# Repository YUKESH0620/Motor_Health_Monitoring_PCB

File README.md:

# Motor Health Monitoring System using 8051

**Embedded Hardware–Firmware Co-Design Project**

---

## Project Overview

The **Motor Health Monitoring System** is an embedded systems project designed to monitor the operational health of an electric motor and protect it from unsafe conditions.

The project integrates:

* A structured hardware design
* Bare-metal embedded control logic
* Simulation-based validation
* Professional documentation practices

The focus is on **learning, reliability, and design clarity**, following workflows commonly used in industry and academia.

---

## System Purpose

* Monitor key motor parameters
* Detect abnormal operating conditions
* Automatically disable the motor under fault
* Provide clear visual and UART-based feedback
* Enable validation without physical hardware

---

## System Operation Flow

* System initialization

* Peripheral setup

* Sensor sampling

* Data filtering

* Threshold comparison

* Fault decision

* Motor control update

* Display & UART update

* Continuous monitoring loop

## Block Diagram

```
Power Input
    │
    V
Voltage Regulation
    │
    V
Microcontroller (8051)
 |--> Sensor Interface
 |   |--> Current
 |   |--> Temperature
 |   |--> Vibration
 |   |--> IR Sensor
 |
 |--> Motor Driver (PWM Control)
 |--> Display (OLED)
 |--> Keypad Interface
 |--> UART Debug Interface
```

---

## System Summary

| Aspect         | Description                         |
| -------------- | ----------------------------------- |
| Controller     | AT89C51 (8051 architecture)         |
| Control Method | Bare-metal                          |
| Sensors        | Current, Temperature, Vibration, IR |
| Motor Control  | PWM-based with fault shutdown       |
| Display        | OLED (I²C)                          |
| User Input     | 4×4 Keypad                          |
| Communication  | UART                                |
| Validation     | Proteus Simulation                  |
| PCB Status     | Not fabricated                      |

---

## Design Artifacts

The repository contains:

* Complete hardware schematics

* PCB layout and 3D models (design stage)

* Proteus simulation files

* Modular firmware source code

* Structured documentation

---

# Schematic Diagram

# PCB Layout

# 3D PCB View

---

## Electrical Specifications

| Parameter                  | Value                         |
|----------------------------|-------------------------------|
| Supply Voltage             | 5 V DC                        |
| MCU Logic Level            | 5 V                           |
| Over-Current Threshold     | 15 A                          |
| Over-Temperature Threshold | 70 °C                         |
| Communication Baud Rate    | Configurable (UART)           |
| Fault Response Time        | Deterministic (loop-based)    |

---

# Simulation_v1

The system was simulated using **Proteus 8.1 Professional software** to validate firmware behavior and system-level logic prior to hardware availability.
The AT89C51 microcontroller, UART interface, motor control logic, fault indicators, and peripheral connections were instantiated according to the schematic.

## Proteus Schematic

Sensor inputs were emulated using adjustable sources to exercise overcurrent and overtemperature fault paths. UART output was used to confirm firmware execution flow and system state transitions. Motor operation was verified logically through enable signals and status indicators rather than physical motor dynamics.

Due to simulator limitations with mixed-signal SPI peripherals on the 8051 core, ADC behavior was validated at firmware logic level. Electrical accuracy of sensor interfaces is planned for validation on physical hardware.

---

## Validation Strategy

* Firmware behavior validated using Proteus simulation at system and logic level

* UART used as the primary observation and debug interface to confirm system states

* Motor control and global shutdown behavior verified through control signals and status indicators

* Fault detection, latching, and recovery logic validated against defined thresholds

* Sensor behavior emulated to exercise fault paths; ADC interface validated at firmware logic level

* Simulation limitations identified and documented; full electrical validation planned on physical hardware

* No dependency on physical PCB availability for firmware and system-level validation

---

## Repository Organization

* **Hardware**
  Contains schematic, PCB, simulation files, and hardware documentation

* **Firmware**
  Contains source code, configuration files, and firmware documentation

Each section includes its own detailed README.

---

## Current Project Status

*  Requirements defined
*  Hardware designed
*  Simulation validated
*  Firmware structured and built
*  PCB fabrication pending

---

## Future Enhancements

* Physical PCB manufacturing
* Bench testing with real motors
* Data logging and diagnostics
* IoT expansion via external gateway
* Advanced fault analytics

---

## Author

**YUKESH**
B.E. Electrical and Electronics Engineering

---

## License

This project is intended for **educational and non-commercial use**.
All materials are shared to support learning, experimentation, and academic review.

---

## Closing Note

This project demonstrates a **complete embedded system lifecycle** - from concept and schematic design to firmware integration and simulation-based validation - following practices aligned with real-world engineering workflows.

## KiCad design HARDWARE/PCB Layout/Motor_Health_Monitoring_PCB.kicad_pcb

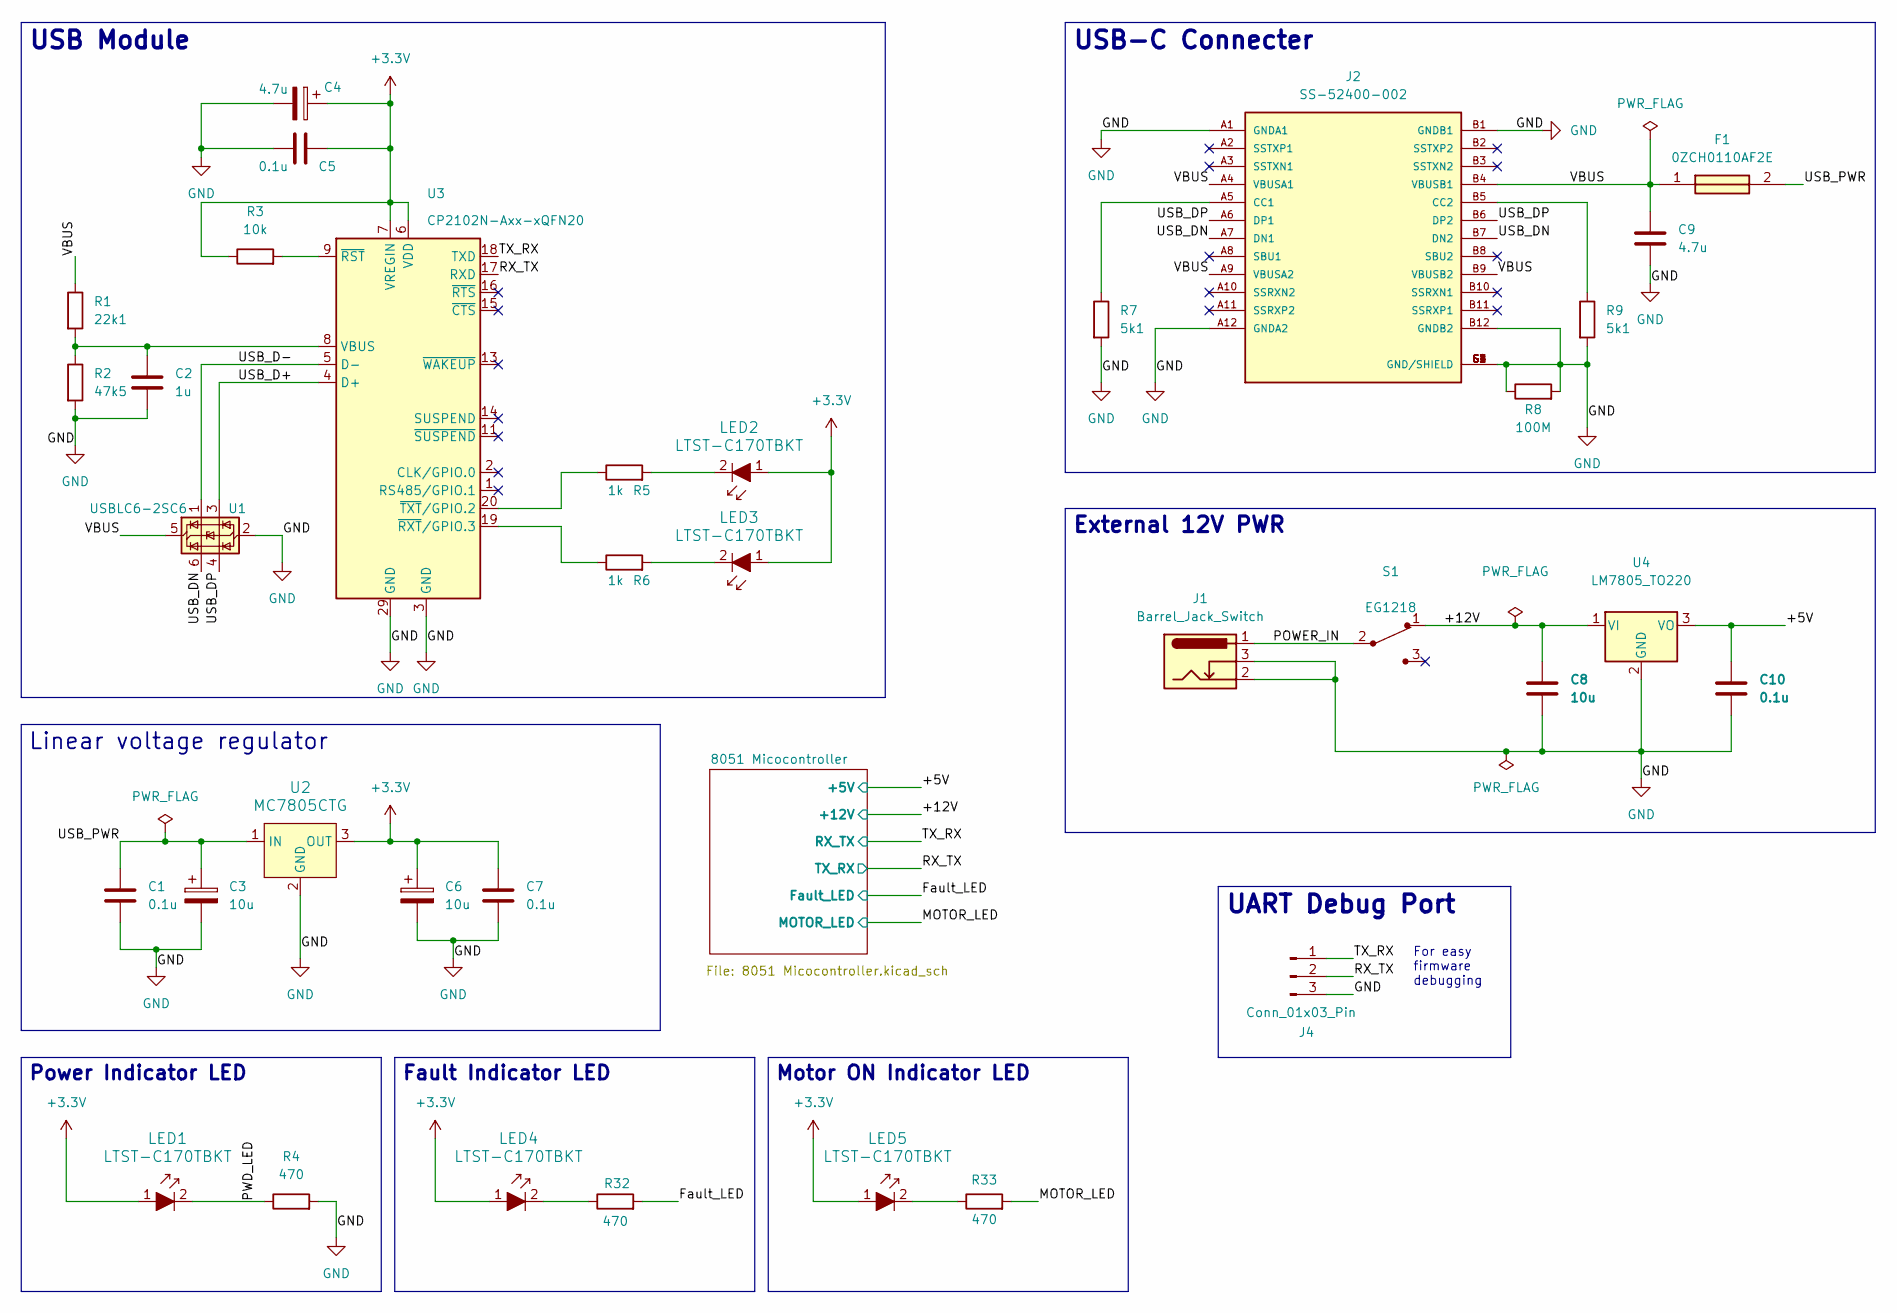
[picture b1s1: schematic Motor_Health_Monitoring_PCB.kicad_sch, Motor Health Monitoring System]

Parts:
C1, C5, C7: 0.1u; C_0805_2012Metric
C2: 1u; C_0805_2012Metric
C3, C6: 10u; T491A
C4: 4.7u; T491A
C8: 10u; C_Disc_D5.0mm_W2.5mm_P2.50mm
C9: 4.7u; C_0805_2012Metric
C10: 0.1u; C_Disc_D5.0mm_W2.5mm_P2.50mm
F1: 0ZCH0110AF2E; FUSC3226X100N; Manufacturer_Part_Number 0ZCH0110AF2E
J1: Barrel_Jack_Switch; BarrelJack_Horizontal
J2: SS-52400-002; BELFUSE_SS-52400-002; PARTREV A0
J4: Conn_01x03_Pin; PinHeader_1x03_P2.54mm_Vertical
LED1, LED2, LED3, LED4, LED5: LTST-C170TBKT; LED_0805_2012Metric_Pad1.15x1.40mm_HandSolder; MPN LTST-C170TBKT; Digi-Key_PN 160-1579-1-ND
R1: 22k1; R_0805_2012Metric
R2: 47k5; R_0805_2012Metric
R3: 10k; R_0805_2012Metric
R4, R32, R33: 470; R_0805_2012Metric
R5, R6: 1k; R_0805_2012Metric
R7, R9: 5k1; R_0805_2012Metric
R8: 100M; R_0805_2012Metric
S1: EG1218; Switch_Slide_11.6x4mm_EG1218; MPN EG1218; Digi-Key_PN EG1903-ND
U1: USBLC6-2SC6; SOT-23-6
U2: MC7805CTG; TO-220-3; MPN MC7805CTG; Digi-Key_PN MC7805CTGOS-ND
U3: CP2102N-Axx-xQFN20; QFN50P500X500X100-29N
U4: LM7805_TO220; TO-220-3_Vertical

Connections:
+3.3V: C4.1, C5.2, C6.1, C7.1, LED1.1, LED2.1, LED3.1, LED4.1, LED5.1, R3.1, U2.3 (OUT), U3.6 (VDD), U3.7 (VREGIN)
/+5V: C10.1, U4.3 (VO); also elsewhere on the board
/+12V: C8.1, S1.1, U4.1 (VI); also elsewhere on the board
/Fault_LED: R32.2; also elsewhere on the board
/MOTOR_LED: R33.2; also elsewhere on the board
/POWER_IN: J1.1, S1.2
/PWD_LED: LED1.2, R4.1
/RX_TX: J4.2, U3.17 (RXD); also elsewhere on the board
/TX_RX: J4.1, U3.18 (TXD); also elsewhere on the board
/USB_D+: U1.3 (I/O2), U3.4 (D+)
/USB_D-: U1.1 (I/O1), U3.5 (D-)
/USB_DN: J2.A7 (DN1), J2.B7 (DN2), U1.6 (I/O1)
/USB_DP: J2.A6 (DP1), J2.B6 (DP2), U1.4 (I/O2)
/USB_PWR: C1.1, C3.1, F1.2, U2.1 (IN)
/VBUS: C9.1, F1.1, J2.A4 (VBUSA1), J2.A9 (VBUSA2), J2.B4 (VBUSB1), J2.B9 (VBUSB2), R1.1, U1.5 (VBUS)
GND: C1.2, C2.2, C3.2, C4.2, C5.1, C6.2, C7.2, C8.2, C9.2, C10.2, J1.2, J1.3, J2.A1 (GNDA1), J2.A12 (GNDA2), J2.B1 (GNDB1), J2.B12 (GNDB2), J2.G1 (GND/SHIELD), J2.G2 (GND/SHIELD), J2.G3 (GND/SHIELD), J2.G4 (GND/SHIELD), J2.S1 (GND/SHIELD), J2.S2 (GND/SHIELD), J2.S3 (GND/SHIELD), J2.S4 (GND/SHIELD), J4.3, R2.2, R4.2, R7.2, R8.1, R8.2, R9.2, U1.2 (GND), U2.2 (GND), U3.3 (GND), U3.12 (GND), U3.21 (GND), U3.29 (GND), U4.2 (GND); also elsewhere on the board
unnamed: J2.A5 (CC1), R7.1
unnamed: J2.B5 (CC2), R9.1
unnamed: LED2.2, R5.2
unnamed: LED3.2, R6.2
unnamed: LED4.2, R32.1
unnamed: LED5.2, R33.1
unnamed: C2.1, R1.2, R2.1, U3.8 (VBUS)
unnamed: R3.2, U3.9 (~RST)
unnamed: R6.1, U3.19 (~RXT/GPIO.3)
unnamed: R5.1, U3.20 (~TXT/GPIO.2)

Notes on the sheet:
For easy firmware debugging
Power Indicator LED
Motor ON Indicator LED
Fault Indicator LED
USB Module
USB-C Connecter
External 12V PWR
UART Debug Port
Linear voltage regulator

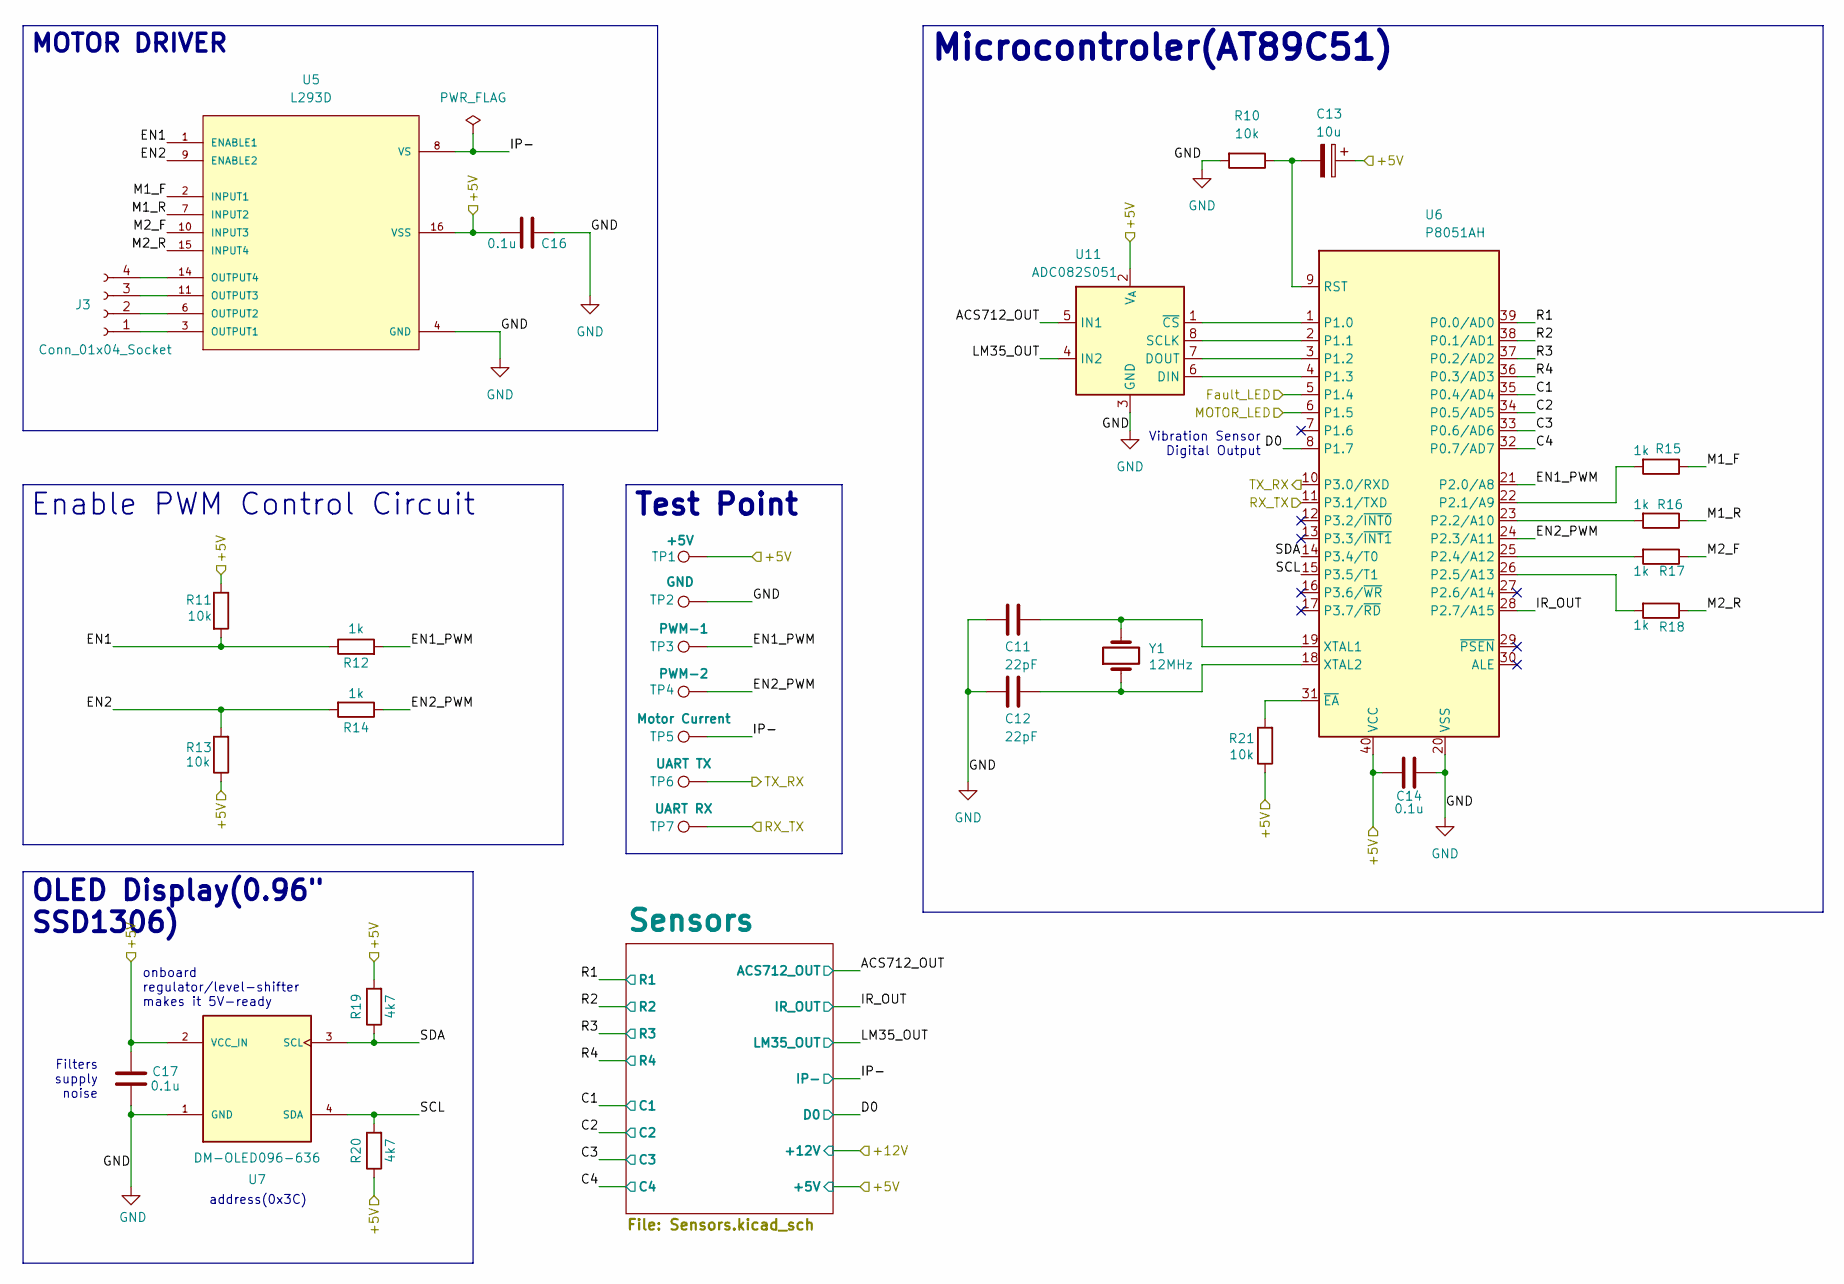
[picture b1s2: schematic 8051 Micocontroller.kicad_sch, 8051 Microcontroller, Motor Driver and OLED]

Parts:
C11, C12: 22pF; C_0805_2012Metric
C13: 10u; C_0805_2012Metric
C14, C16, C17: 0.1u; C_0805_2012Metric
J3: Conn_01x04_Socket; TerminalBlock_Phoenix_PT-1,5-4-5.0-H_1x04_P5.00mm_Horizontal
R10, R11, R13, R21: 10k; R_0805_2012Metric
R12, R14, R15, R16, R17, R18: 1k; R_0805_2012Metric
R19, R20: 4k7; R_0805_2012Metric
TP1: +5V; TestPoint_Pad_D2.0mm
TP2: GND; TestPoint_Pad_D2.0mm
TP3: PWM-1; TestPoint_Pad_D2.0mm
TP4: PWM-2; TestPoint_Pad_D2.0mm
TP5: Motor Current; TestPoint_Pad_D2.0mm
TP6: UART TX; TestPoint_Pad_D2.0mm
TP7: UART RX; TestPoint_Pad_D2.0mm
U5: L293D; DIP880W50P254L2000H510Q16
U6: P8051AH; DIP-40_W15.24mm
U7: DM-OLED096-636; MODULE_DM-OLED096-636; PARTREV 2018-09-10
U11: ADC082S051; VSSOP-8_3x3mm_P0.65mm
Y1: 12MHz; Crystal_SMD_5032-2Pin_5.0x3.2mm_HandSoldering

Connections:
/8051 Micocontroller/ACS712_OUT: U11.5 (IN1); also elsewhere on the board
/8051 Micocontroller/C1: U6.35 (P0.4/AD4); also elsewhere on the board
/8051 Micocontroller/C2: U6.34 (P0.5/AD5); also elsewhere on the board
/8051 Micocontroller/C3: U6.33 (P0.6/AD6); also elsewhere on the board
/8051 Micocontroller/C4: U6.32 (P0.7/AD7); also elsewhere on the board
/8051 Micocontroller/D0: U6.8 (P1.7); also elsewhere on the board
/8051 Micocontroller/EN1: R11.2, R12.1, U5.1 (ENABLE1)
/8051 Micocontroller/EN1_PWM: R12.2, TP3.1, U6.21 (P2.0/A8)
/8051 Micocontroller/EN2: R13.2, R14.2, U5.9 (ENABLE2)
/8051 Micocontroller/EN2_PWM: R14.1, TP4.1, U6.24 (P2.3/A11)
/8051 Micocontroller/IP-: TP5.1, U5.8 (VS); also elsewhere on the board
/8051 Micocontroller/IR_OUT: U6.28 (P2.7/A15); also elsewhere on the board
/8051 Micocontroller/LM35_OUT: U11.4 (IN2); also elsewhere on the board
/8051 Micocontroller/M1_F: R15.1, U5.2 (INPUT1)
/8051 Micocontroller/M1_R: R16.1, U5.7 (INPUT2)
/8051 Micocontroller/M2_F: R17.1, U5.10 (INPUT3)
/8051 Micocontroller/M2_R: R18.1, U5.15 (INPUT4)
/8051 Micocontroller/R1: U6.39 (P0.0/AD0); also elsewhere on the board
/8051 Micocontroller/R2: U6.38 (P0.1/AD1); also elsewhere on the board
/8051 Micocontroller/R3: U6.37 (P0.2/AD2); also elsewhere on the board
/8051 Micocontroller/R4: U6.36 (P0.3/AD3); also elsewhere on the board
/8051 Micocontroller/SCL: R20.2, U6.15 (P3.5/T1), U7.4 (SDA)
/8051 Micocontroller/SDA: R19.1, U6.14 (P3.4/T0), U7.3 (SCL)
/+5V: C13.1, C14.1, C16.1, C17.2, R11.1, R13.1, R19.2, R20.1, R21.1, TP1.1, U5.16 (VSS), U6.40 (VCC), U7.2 (VCC_IN), U11.2 (V_{A}); also elsewhere on the board
/Fault_LED: U6.5 (P1.4); also elsewhere on the board
/MOTOR_LED: U6.6 (P1.5); also elsewhere on the board
/RX_TX: TP6.1, U6.10 (P3.0/RXD); also elsewhere on the board
/TX_RX: TP7.1, U6.11 (P3.1/TXD); also elsewhere on the board
GND: C11.2, C12.2, C14.2, C16.2, C17.1, R10.2, TP2.1, U5.4 (GND), U5.5 (GND), U5.12 (GND), U5.13 (GND), U6.20 (VSS), U7.1 (GND), U11.3 (GND); also elsewhere on the board
unnamed: J3.1, U5.3 (OUTPUT1)
unnamed: J3.2, U5.6 (OUTPUT2)
unnamed: J3.3, U5.11 (OUTPUT3)
unnamed: J3.4, U5.14 (OUTPUT4)
unnamed: R15.2, U6.22 (P2.1/A9)
unnamed: R16.2, U6.23 (P2.2/A10)
unnamed: R17.2, U6.25 (P2.4/A12)
unnamed: R18.2, U6.26 (P2.5/A13)
unnamed: C13.2, R10.1, U6.9 (RST)
unnamed: C11.1, U6.19 (XTAL1), Y1.2
unnamed: C12.1, U6.18 (XTAL2), Y1.1
unnamed: R21.2, U6.31 (~EA)
unnamed: U6.4 (P1.3), U11.6 (DIN)
unnamed: U6.3 (P1.2), U11.7 (DOUT)
unnamed: U6.2 (P1.1), U11.8 (SCLK)
unnamed: U6.1 (P1.0), U11.1 (~CS)

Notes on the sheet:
onboard regulator/level-shifter makes it 5V-ready
address(0x3C)
Vibration Sensor Digital Output
Filters supply noise
Test Point
MOTOR DRIVER
Microcontroler(AT89C51)
Enable PWM Control Circuit
OLED Display(0.96" SSD1306)

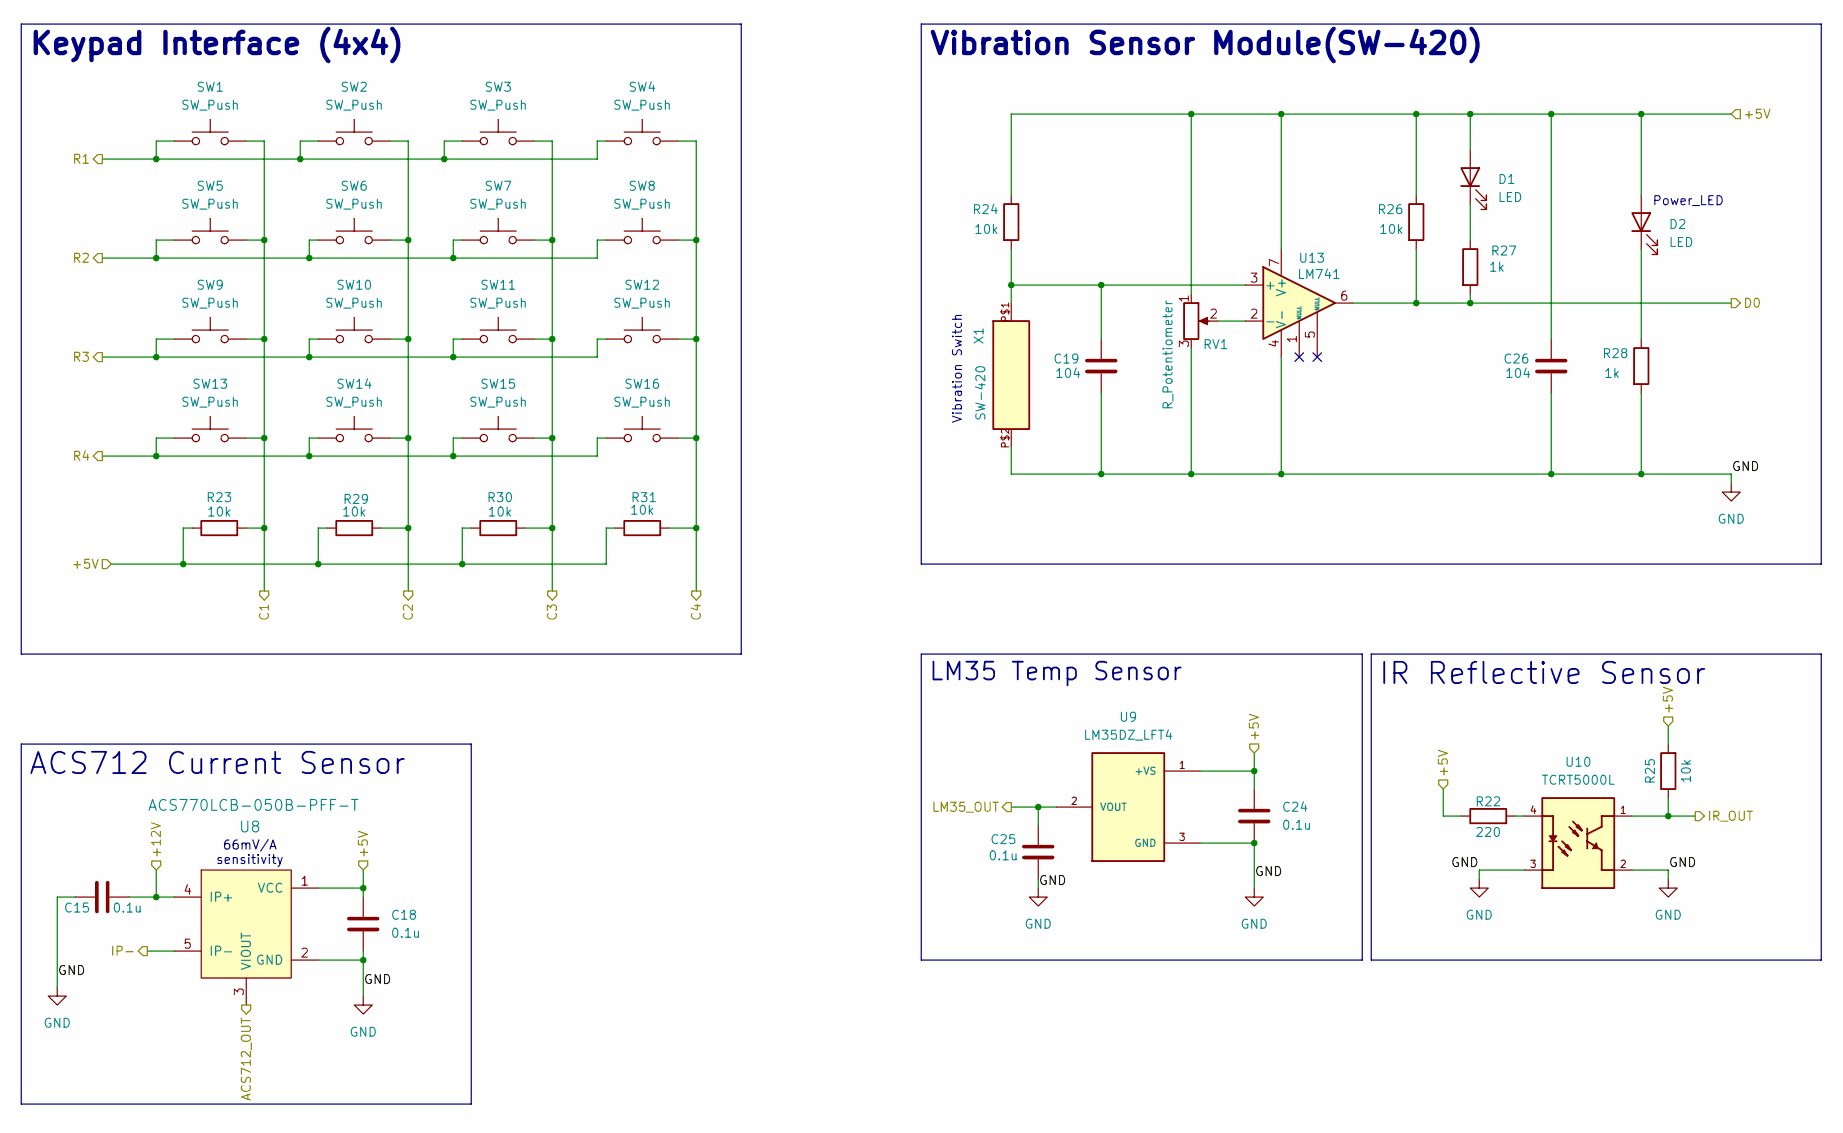
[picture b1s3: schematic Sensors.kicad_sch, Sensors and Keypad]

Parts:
C15, C18, C24, C25: 0.1u; C_0805_2012Metric
C19, C26: 104; C_0805_2012Metric
D1, D2: LED; LED_0805_2012Metric_Pad1.15x1.40mm_HandSolder
R22: 220; R_0805_2012Metric
R23, R24, R25, R26, R29, R30, R31: 10k; R_0805_2012Metric
R27, R28: 1k; R_0805_2012Metric
RV1: R_Potentiometer; Potentiometer_Bourns_3266Y_Vertical
SW1, SW2, SW3, SW4, SW5, SW6, SW7, SW8, SW9, SW10, SW11, SW12, SW13, SW14, SW15, SW16: SW_Push; SW_PUSH_1P1T_6x3.5mm_H5.0_APEM_MJTP1250
U8: ACS770LCB-050B-PFF-T; CB-5_Formed_Leads; MPN ACS770LCB-050B-PFF-T; Digi-Key_PN 620-1541-5-ND
U9: LM35DZ_LFT4; IC_LM35DZ_LFT4; PARTREV H
U10: TCRT5000L; XDCR_TCRT5000L
U13: LM741; DIP794W45P254L959H508Q8
X1: SW-420

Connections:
/8051 Micocontroller/ACS712_OUT: U8.3 (VIOUT); also elsewhere on the board
/8051 Micocontroller/C1: R23.2, SW1.2, SW5.2, SW9.2, SW13.2; also elsewhere on the board
/8051 Micocontroller/C2: R29.2, SW2.2, SW6.2, SW10.2, SW14.2; also elsewhere on the board
/8051 Micocontroller/C3: R30.2, SW3.2, SW7.2, SW11.2, SW15.2; also elsewhere on the board
/8051 Micocontroller/C4: R31.2, SW4.2, SW8.2, SW12.2, SW16.2; also elsewhere on the board
/8051 Micocontroller/D0: R26.2, R27.2, U13.6; also elsewhere on the board
/8051 Micocontroller/IP-: U8.5 (IP-); also elsewhere on the board
/8051 Micocontroller/IR_OUT: R25.1, U10.1; also elsewhere on the board
/8051 Micocontroller/LM35_OUT: C25.1, U9.2 (VOUT); also elsewhere on the board
/8051 Micocontroller/R1: SW1.1, SW2.1, SW3.1, SW4.1; also elsewhere on the board
/8051 Micocontroller/R2: SW5.1, SW6.1, SW7.1, SW8.1; also elsewhere on the board
/8051 Micocontroller/R3: SW9.1, SW10.1, SW11.1, SW12.1; also elsewhere on the board
/8051 Micocontroller/R4: SW13.1, SW14.1, SW15.1, SW16.1; also elsewhere on the board
/+5V: C18.1, C24.1, C26.1, D1.2 (A), D2.2 (A), R22.1, R23.1, R24.1, R25.2, R26.1, R29.1, R30.1, R31.1, RV1.1, U8.1 (VCC), U9.1 (+VS), U13.7 (V+); also elsewhere on the board
/+12V: C15.1, U8.4 (IP+); also elsewhere on the board
GND: C15.2, C18.2, C19.2, C24.2, C25.2, C26.2, R28.2, RV1.3, U8.2 (GND), U9.3 (GND), U10.2, U10.3, U13.4 (V-), X1.P$2; also elsewhere on the board
unnamed: D1.1 (K), R27.1
unnamed: D2.1 (K), R28.1
unnamed: R22.2, U10.4
unnamed: C19.1, R24.2, U13.3 (+), X1.P$1
unnamed: RV1.2, U13.2 (-)

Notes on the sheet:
Vibration Switch
Power_LED
66mV/A sensitivity
ACS712 Current Sensor
Vibration Sensor Module(SW-420)
IR Reflective Sensor
LM35 Temp Sensor
Keypad Interface (4x4)

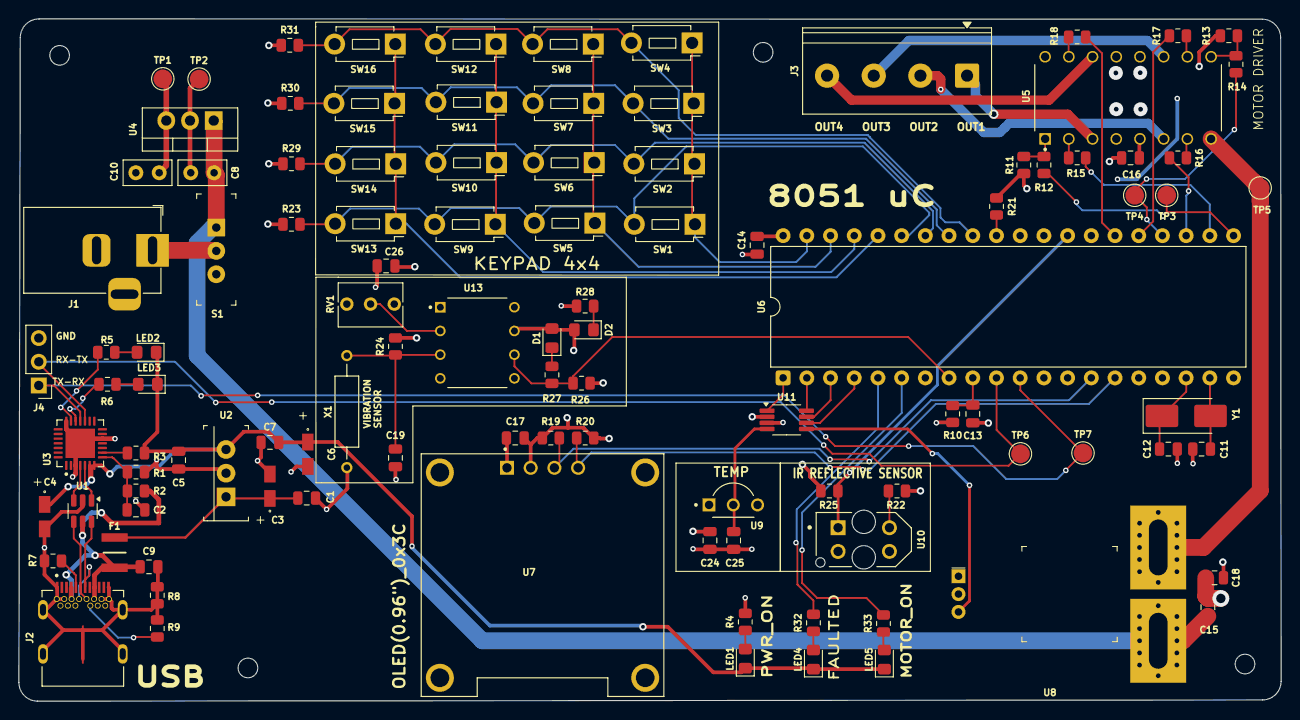
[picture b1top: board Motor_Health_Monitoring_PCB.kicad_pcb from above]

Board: 4 copper layers, 135.2 x 73.1 mm, 106 parts (0 on the bottom side), 70 nets.

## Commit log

2026-01-16 Initial hardware project upload
2026-01-16 Cleanup: remove KiCad backups and cache files
2026-01-16 Add .gitignore for Kicad project
2026-01-16 Ignore KiCad runtime and cache files
2026-01-17 Add initial firmware architecture and hardware BOM
2026-01-24 Validation files added and changes saved
2026-01-24 Fix formatting of error responses in uart_protocol.md
2026-01-24 Add Schematic_png.md with image reference
2026-01-24 Ignore sd file using .gitignore
2026-01-24 Revise README for Simulation v2 and Proteus details
    Updated README to reflect changes in simulation versioning and validation details.
